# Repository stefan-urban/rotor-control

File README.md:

Rotor control with BeagleBone Black
===================================

Dieses Projekt entstand als Teil meiner Bachelorarbeit. Es zielt darauf ab ein Interface für zwei Antennenrotoren (unterschiedlicher Hersteller) zu bauen. Dieses soll eine Schnittstelle zu hamlib besitzen.

Vorraussetzungen
----------------

Hardware
- BeagleBone Black (=BBB)
- Cape wie unter dem Ordner `/hardware/eagle-project`
- Rotoren:
 - Create ERC5A (Elevation)
 - Yaesu G-2800DXC (Azimuth)

Software
- Debian 7.x mit
 - libpcre3-dev
 - libconfig-dev
 - libhamlib-utils (beinhaltet rotctl, rotctld)
- Auf dem Host-PC
 - Gpredict

Installation & Inbetriebnahme
-----------------------------

1. Software (unter `/software/`) aus diesem Repository in beliebigen Ordner auf dem BBB speichern.

2. (Optional) Konfigurationsfile unter `/etc/rotor_control.conf` anlegen. Eine Beispielkonfiguration ist im Ornder `docs` beigelegt.

3. (Optional) Rsyslogd konfigurieren.

 Standardmäßig werden alle Logging-Meldungen in `/var/log/syslog` mit allen anderen Meldungen vom System vermischt. Wie unser Programm ein eigene Logging-Datei erhält wird im beiliegenen Dokument [syslog.md](docs/syslog.md) erklärt.

5. Installieren
 ```
 debian@beaglebone:~/code/rotor-control/software$ sudo ./scripts/install.sh
 ```

 Jetzt werden alle erforderlichen Dateien in die entsprechenden Verzeichnise kopiert:
 - Programm und Start/Stop-Skripte nach `/opt/rotor-control/`
 - Daemon nach `/etc/init.d/`

6. Dienst starten
 ```
 debian@beaglebone:~/code/rotor-control/software$ sudo service rotor-control start
 ```

8. Verbindung mit gPredict aufbauen

 8.1. Gpredict starten
 
 8.2. Unter _Bearbeiten_ > _Einstellungen_ > _Interfaces_ > _Rotators_ einen neuen Rotor hinzufügen.
 
 8.3 Im Hauptfenster rechts oben auf den nach unten zeigenden Pfeil drücken und im erscheinenen Menü _Antennenkontrolle_ auswählen
 
 8.4 Es erscheint folgendes Fenster:

 8.5 Mit Drücken von _Kontakt_ wird die Verbindung zum BBB hergestellt und versucht die eingestellt Position anzufahren.

Verwendung ohne Rotoren
-----------------------

Zum Debugging ist es oft hilfreich das Programm __ohne__ die Rotorenanbindung zu betreiben. Dies ist möglich wenn in der Konfiguration die Simulation eingeschaltet wird. Dann wie oben beschrieben vorgehen.

Hintergrund: Als Rotorenansteuerung kommen jetzt nicht diverse GPIOs und ADCs zum Einsatz, welche es auf PCs gar nicht gibt, sondern ein Simulator.

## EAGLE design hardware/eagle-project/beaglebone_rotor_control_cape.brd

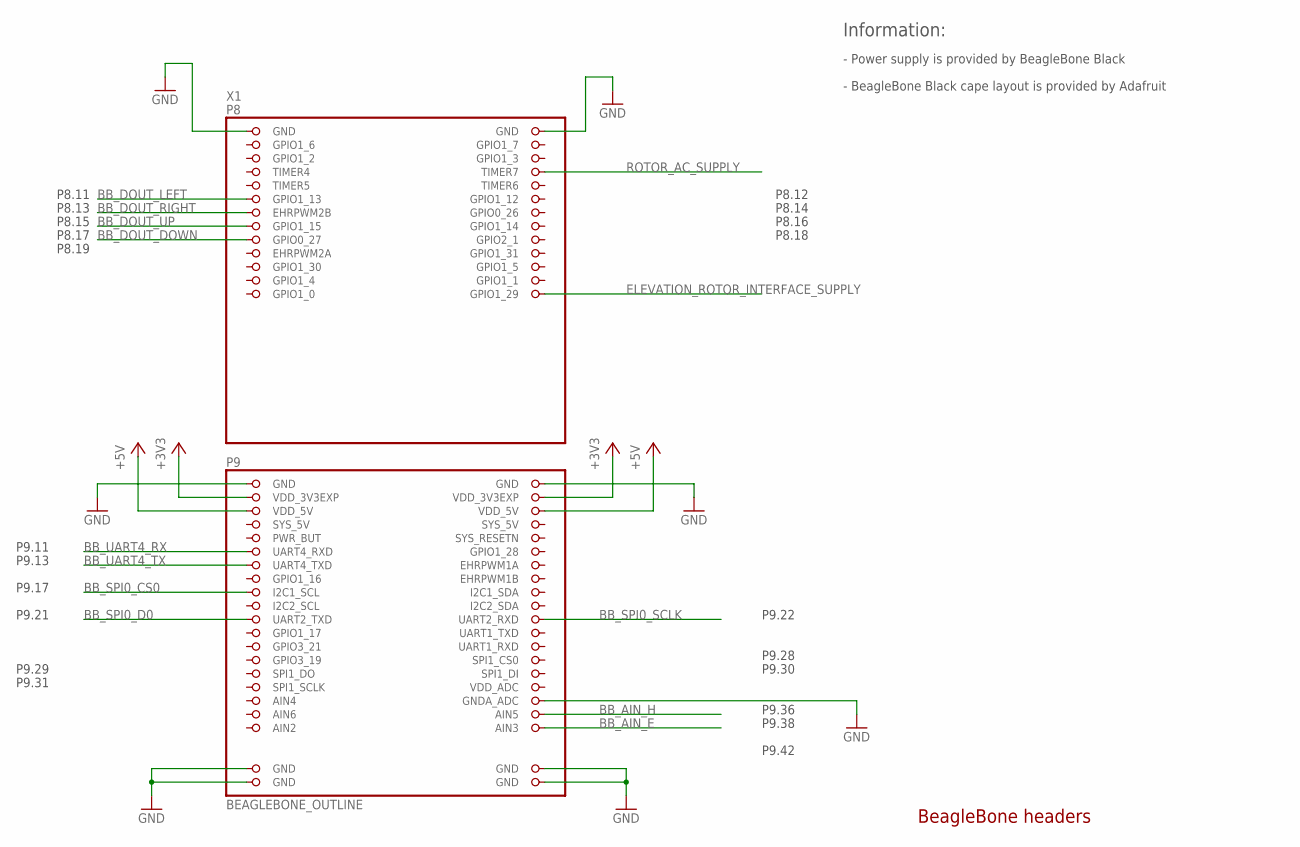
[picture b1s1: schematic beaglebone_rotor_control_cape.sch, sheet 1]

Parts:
X1: BEAGLEBONE_OUTLINE; BEAGLEBONE_SHIELD

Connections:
+3V3: X1.49 (VDD_3V3EXP), X1.50 (VDD_3V3EXP); also elsewhere on the board
+5V: X1.51 (VDD_5V), X1.52 (VDD_5V); also elsewhere on the board
BB_AIN_E: X1.84 (AIN3); also elsewhere on the board
BB_AIN_H: X1.82 (AIN5); also elsewhere on the board
BB_DOUT_DOWN: X1.17 (GPIO0_27); also elsewhere on the board
BB_DOUT_LEFT: X1.11 (GPIO1_13); also elsewhere on the board
BB_DOUT_RIGHT: X1.13 (EHRPWM2B); also elsewhere on the board
BB_DOUT_UP: X1.15 (GPIO1_15); also elsewhere on the board
BB_SPI0_CS0: X1.63 (I2C1_SCL); also elsewhere on the board
BB_SPI0_D0: X1.67 (UART2_TXD); also elsewhere on the board
BB_SPI0_SCLK: X1.68 (UART2_RXD); also elsewhere on the board
BB_UART4_RX: X1.57 (UART4_RXD); also elsewhere on the board
BB_UART4_TX: X1.59 (UART4_TXD); also elsewhere on the board
ELEVATION_ROTOR_INTERFACE_SUPPLY: X1.26 (GPIO1_29); also elsewhere on the board
GND: X1.1 (GND), X1.2 (GND), X1.47 (GND), X1.48 (GND), X1.80 (GNDA_ADC), X1.89 (GND), X1.90 (GND), X1.91 (GND), X1.92 (GND); also elsewhere on the board
ROTOR_AC_SUPPLY: X1.8 (TIMER7); also elsewhere on the board
SYS_5V: X1.53 (SYS_5V)

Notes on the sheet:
BeagleBone headers
- Power supply is provided by BeagleBone Black
Information:
- BeagleBone Black cape layout is provided by Adafruit
P9.17
P9.22
P9.21
P9.13
P9.11
P9.29
P9.30
P9.31
P9.28
P8.11
P8.13
P8.15
P8.17
P8.19
P8.12
P8.14
P8.16
P8.18
P9.36
P9.38
P9.42

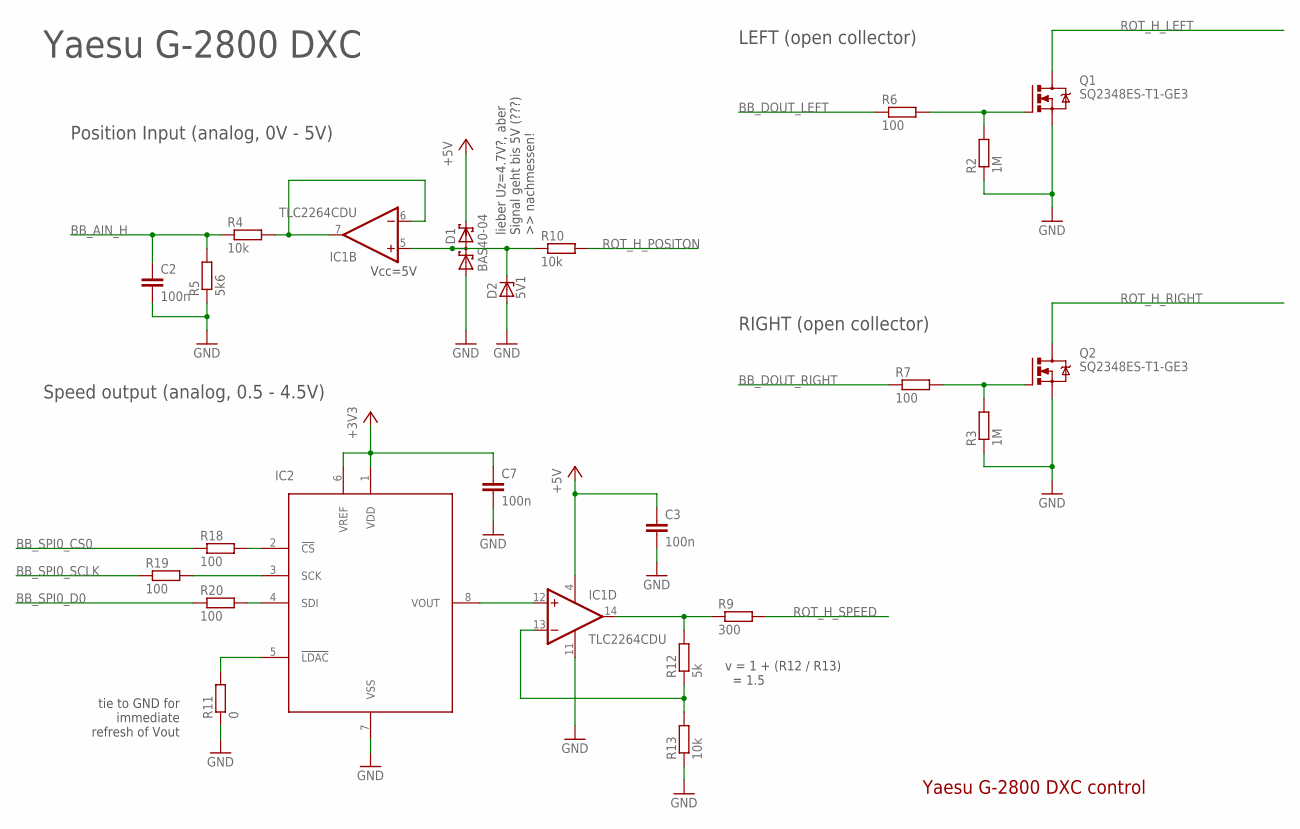
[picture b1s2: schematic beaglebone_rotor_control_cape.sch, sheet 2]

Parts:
C2, C3, C7: 100n; C0603
D1: BAS40-04; SOT23
D2: 5V1; SOT23
IC1: TLC2264CDU; SO14
IC2: MCP4901; SO-08
Q1, Q2: SQ2348ES-T1-GE3; SOT23
R2, R3: 1M; R0805
R4, R10, R13: 10k; R0805
R5: 5k6; R0805
R6, R7, R18, R19, R20: 100; R0805
R9: 300; R0805
R11: 0; R0805
R12: 5k; R0805

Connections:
+3V3: C7.1, IC2.1 (VDD), IC2.6 (VREF); also elsewhere on the board
+5V: C3.1, D1.2 (C2), IC1.4 (V+); also elsewhere on the board
BB_AIN_H: C2.1, R4.1, R5.2; also elsewhere on the board
BB_DOUT_LEFT: R6.1; also elsewhere on the board
BB_DOUT_RIGHT: R7.1; also elsewhere on the board
BB_SPI0_CS0: R18.1; also elsewhere on the board
BB_SPI0_D0: R20.1; also elsewhere on the board
BB_SPI0_SCLK: R19.1; also elsewhere on the board
GND: C2.2, C3.2, C7.2, D1.1 (A1), D2.1 (A), IC1.11 (V-), IC2.7 (VSS), Q1.2 (S), Q2.2 (S), R2.1, R3.1, R5.1, R11.1, R13.1; also elsewhere on the board
unnamed: IC1.6 (-IN), IC1.7 (OUT), R4.2
unnamed: IC1.12 (+IN), IC2.8 (VOUT)
unnamed: IC1.14 (OUT), R9.1, R12.2
unnamed: IC1.13 (-IN), R12.1, R13.2
unnamed: IC2.2 (!CS), R18.2
unnamed: IC2.5 (!LDAC), R11.2
unnamed: IC2.4 (SDI), R20.2
unnamed: IC2.3 (SCK), R19.2
unnamed: Q2.1 (G), R3.2, R7.2
unnamed: D1.3 (C1A2), D2.3 (C), IC1.5 (+IN), R10.1
unnamed: Q1.1 (G), R2.2, R6.2
ROT_H_LEFT: Q1.3 (D); also elsewhere on the board
ROT_H_POSITON: R10.2; also elsewhere on the board
ROT_H_RIGHT: Q2.3 (D); also elsewhere on the board
ROT_H_SPEED: R9.2; also elsewhere on the board

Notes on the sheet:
Yaesu G-2800 DXC control
LEFT (open collector)
RIGHT (open collector)
Position Input (analog, 0V - 5V)
Yaesu G-2800 DXC
Speed output (analog, 0.5 - 4.5V)
lieber Uz=4.7V?, aber Signal geht bis 5V (???) >> nachmessen!
Vcc=5V
tie to GND for immediate refresh of Vout
v = 1 + (R12 / R13) = 1.5

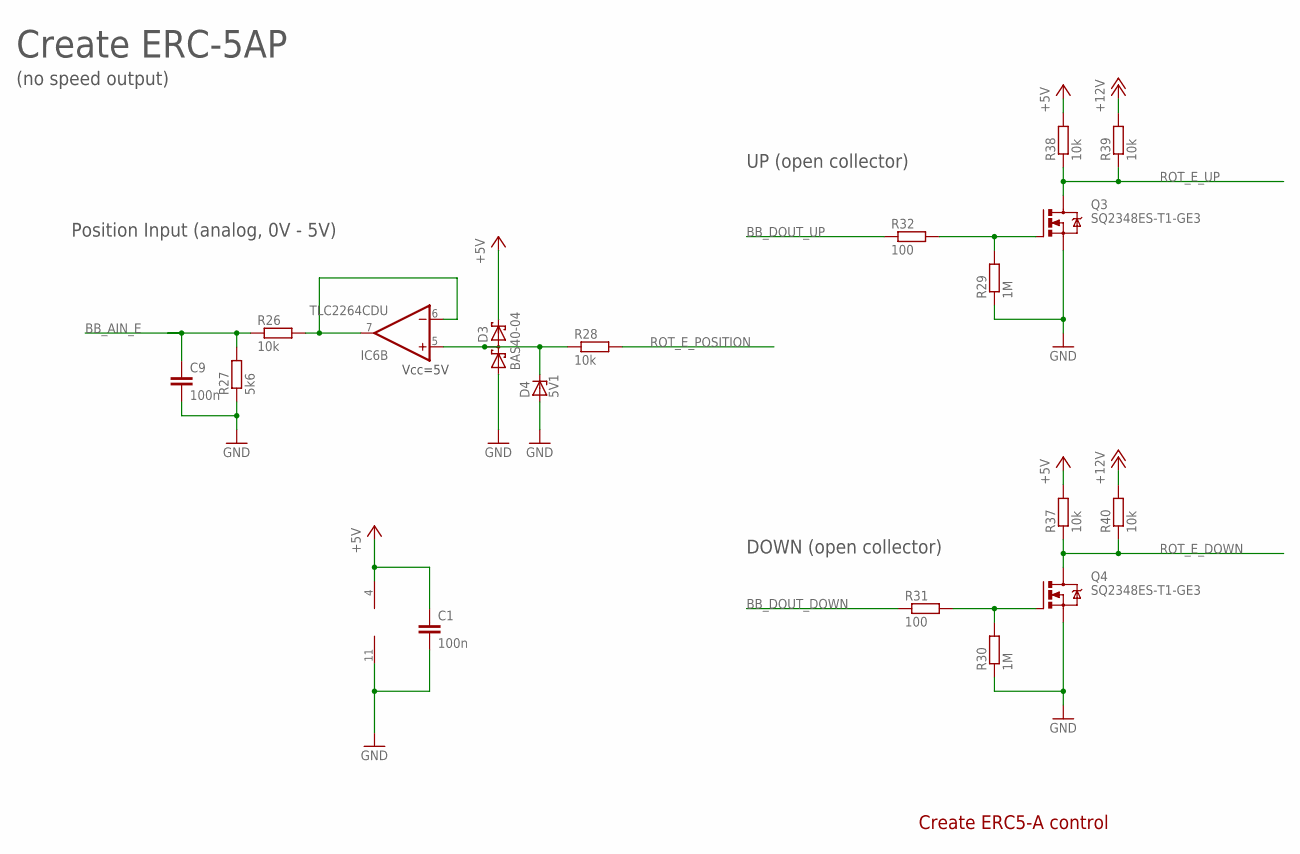
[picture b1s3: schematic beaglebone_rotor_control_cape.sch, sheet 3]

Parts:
C1, C9: 100n; C0603
D3: BAS40-04; SOT23
D4: 5V1; SOT23
IC6: TLC2264CDU; SO14
Q3, Q4: SQ2348ES-T1-GE3; SOT23
R26, R28, R37, R38, R39, R40: 10k; R0805
R27: 5k6; R0805
R29, R30: 1M; R0805
R31, R32: 100; R0805

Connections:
+5V: C1.1, D3.2 (C2), IC6.4 (V+), R37.2, R38.2; also elsewhere on the board
+12V: R39.2, R40.2; also elsewhere on the board
BB_AIN_E: C9.1, R26.1, R27.2; also elsewhere on the board
BB_DOUT_DOWN: R31.1; also elsewhere on the board
BB_DOUT_UP: R32.1; also elsewhere on the board
GND: C1.2, C9.2, D3.1 (A1), D4.1 (A), IC6.11 (V-), Q3.2 (S), Q4.2 (S), R27.1, R29.1, R30.1; also elsewhere on the board
unnamed: IC6.6 (-IN), IC6.7 (OUT), R26.2
unnamed: D3.3 (C1A2), D4.3 (C), IC6.5 (+IN), R28.1
unnamed: Q3.1 (G), R29.2, R32.2
unnamed: Q4.1 (G), R30.2, R31.2
ROT_E_DOWN: Q4.3 (D), R37.1, R40.1; also elsewhere on the board
ROT_E_POSITION: R28.2; also elsewhere on the board
ROT_E_UP: Q3.3 (D), R38.1, R39.1; also elsewhere on the board

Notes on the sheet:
Create ERC5-A control
Position Input (analog, 0V - 5V)
Vcc=5V
Create ERC-5AP
UP (open collector)
DOWN (open collector)
(no speed output)

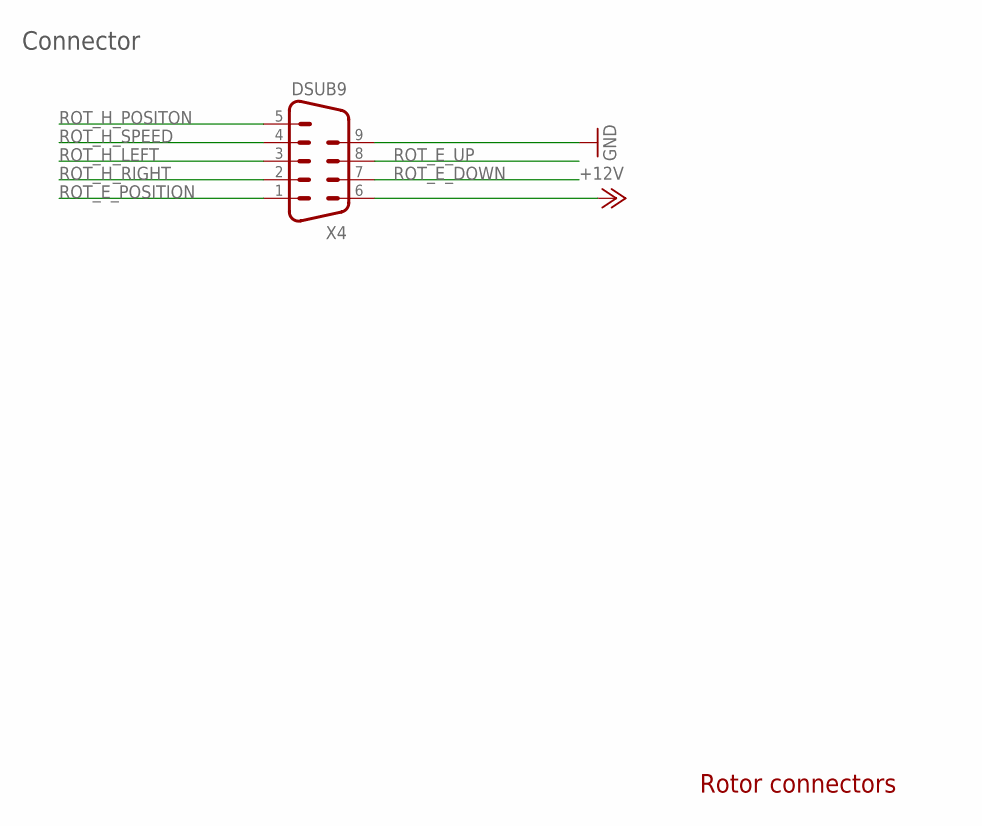
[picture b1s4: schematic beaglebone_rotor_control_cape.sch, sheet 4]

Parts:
X4: DSUB9

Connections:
+12V: X4.6; also elsewhere on the board
GND: X4.9; also elsewhere on the board
ROT_E_DOWN: X4.7; also elsewhere on the board
ROT_E_POSITION: X4.1; also elsewhere on the board
ROT_E_UP: X4.8; also elsewhere on the board
ROT_H_LEFT: X4.3; also elsewhere on the board
ROT_H_POSITON: X4.5; also elsewhere on the board
ROT_H_RIGHT: X4.2; also elsewhere on the board
ROT_H_SPEED: X4.4; also elsewhere on the board

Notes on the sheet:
Rotor connectors
Connector

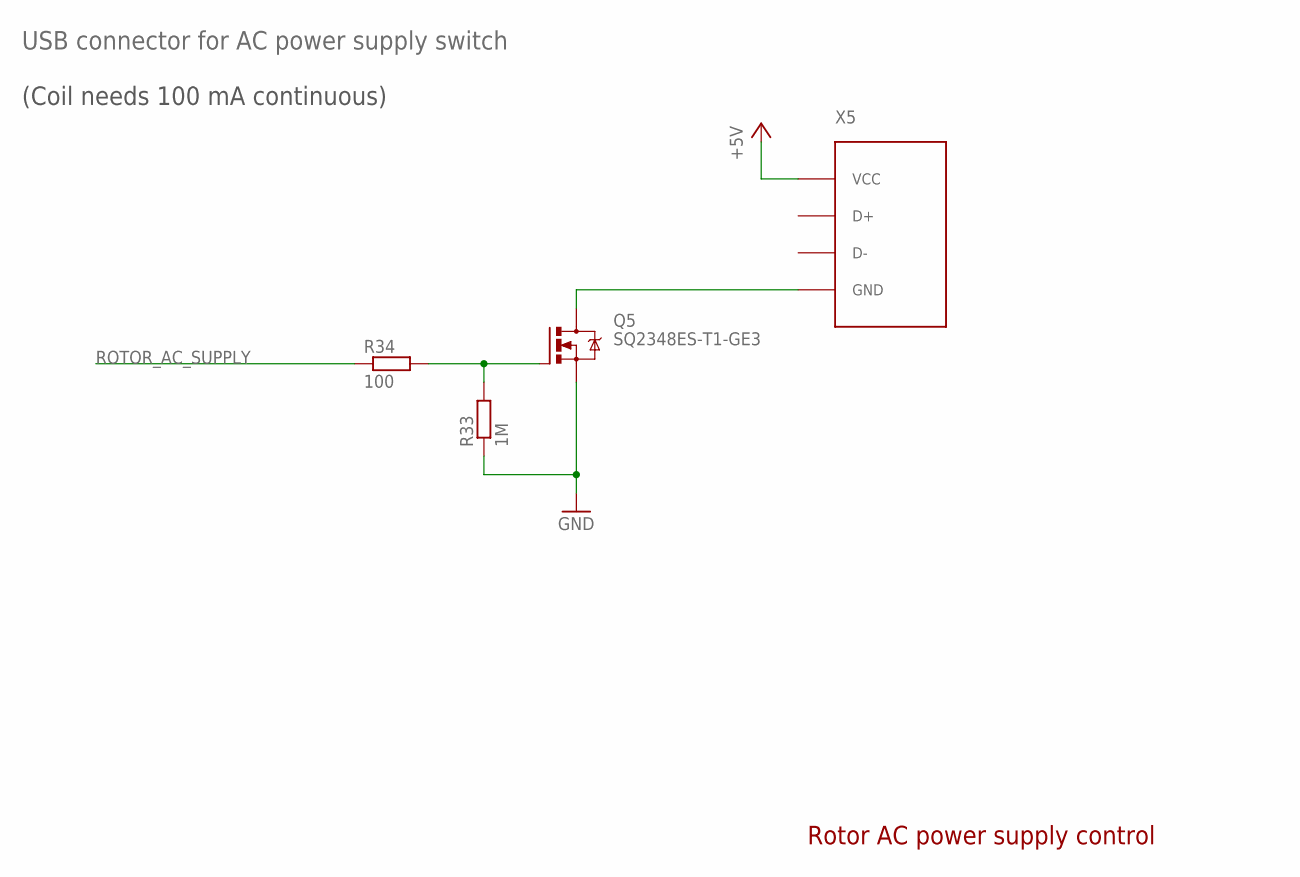
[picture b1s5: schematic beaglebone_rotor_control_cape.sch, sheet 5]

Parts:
Q5: SQ2348ES-T1-GE3; SOT23
R33: 1M; R0805
R34: 100; R0805
X5: USBDEV; USB

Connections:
+5V: X5.1-VCC (VCC); also elsewhere on the board
GND: Q5.2 (S), R33.1; also elsewhere on the board
unnamed: Q5.3 (D), X5.GND
unnamed: Q5.1 (G), R33.2, R34.2
ROTOR_AC_SUPPLY: R34.1; also elsewhere on the board

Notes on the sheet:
Rotor AC power supply control
USB connector for AC power supply switch
(Coil needs 100 mA continuous)

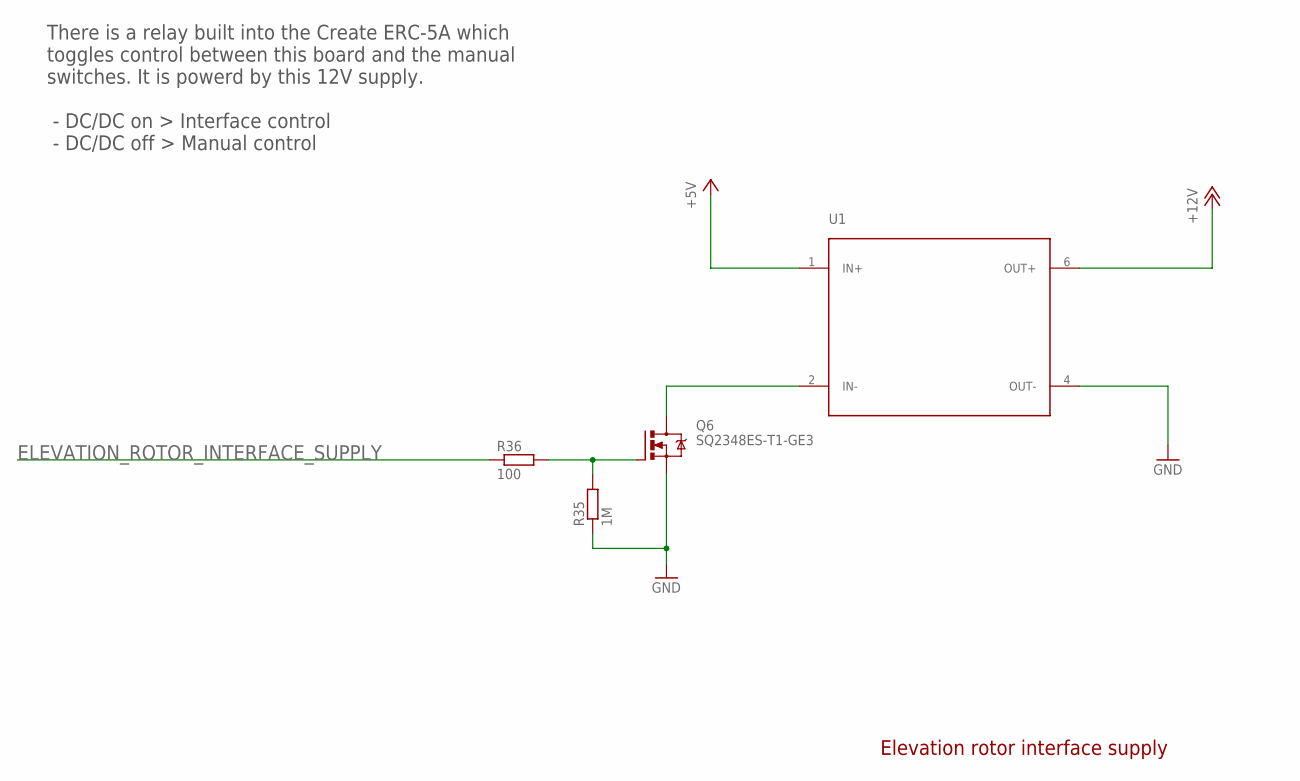
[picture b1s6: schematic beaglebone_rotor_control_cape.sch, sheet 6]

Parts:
Q6: SQ2348ES-T1-GE3; SOT23
R35: 1M; R0805
R36: 100; R0805
U1: TMH0512S; SIP

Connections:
+5V: U1.1 (IN+); also elsewhere on the board
+12V: U1.6 (OUT+); also elsewhere on the board
ELEVATION_ROTOR_INTERFACE_SUPPLY: R36.1; also elsewhere on the board
GND: Q6.2 (S), R35.1, U1.4 (OUT-); also elsewhere on the board
unnamed: Q6.1 (G), R35.2, R36.2
unnamed: Q6.3 (D), U1.2 (IN-)

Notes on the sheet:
Elevation rotor interface supply
There is a relay built into the Create ERC-5A which toggles control between this board and the manual switches. It is powerd by this 12V supply. - DC/DC on > Interface control - DC/DC off > Manual control

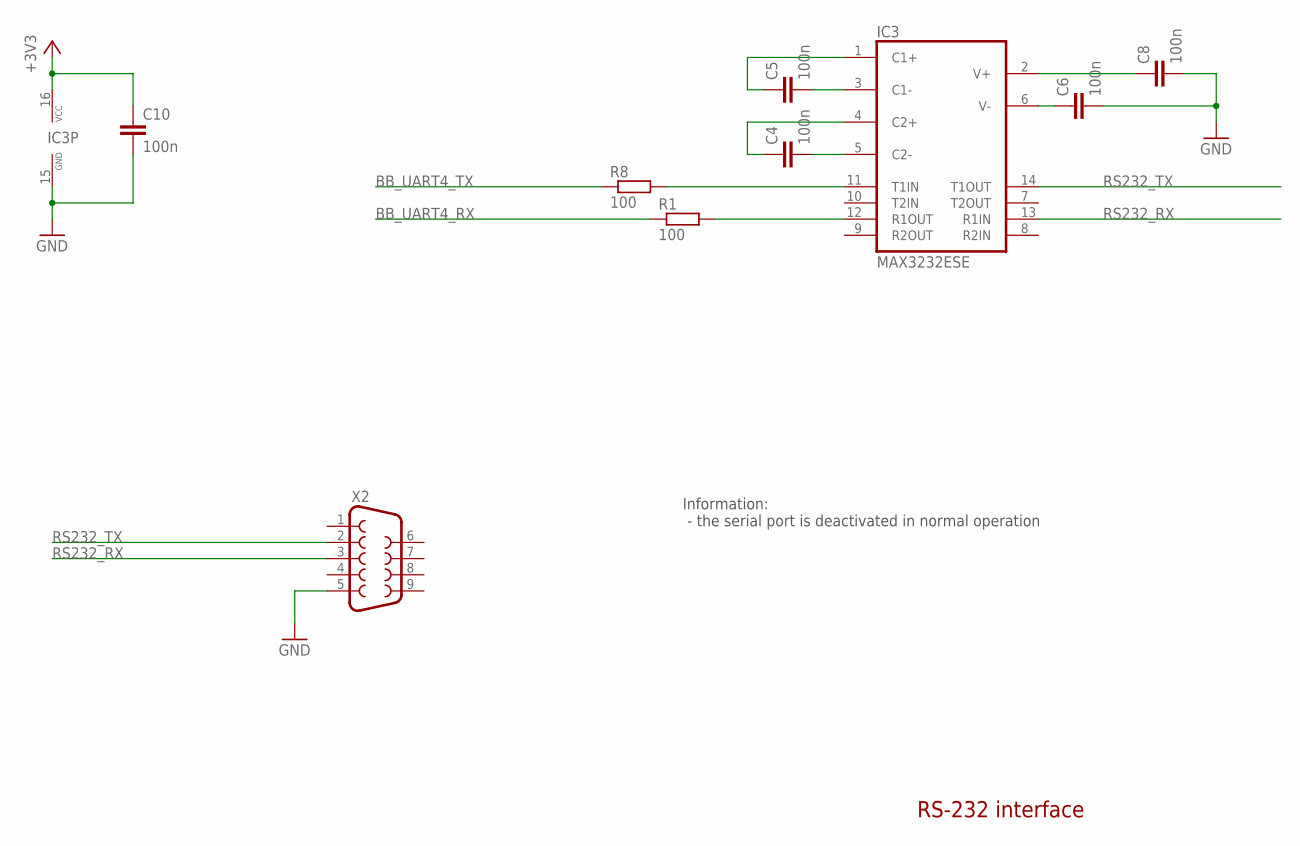
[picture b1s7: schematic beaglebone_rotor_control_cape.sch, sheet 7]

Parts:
C4, C5, C6, C8, C10: 100n; C0603
IC3: MAX3232ESE; SO16
R1, R8: 100; R0805
X2: F09VP

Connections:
+3V3: C10.1, IC3.16 (VCC); also elsewhere on the board
BB_UART4_RX: R1.1; also elsewhere on the board
BB_UART4_TX: R8.1; also elsewhere on the board
GND: C6.2, C8.2, C10.2, IC3.15 (GND), X2.5; also elsewhere on the board
unnamed: C4.1, IC3.4 (C2+)
unnamed: C4.2, IC3.5 (C2-)
unnamed: C5.2, IC3.3 (C1-)
unnamed: C5.1, IC3.1 (C1+)
unnamed: C6.1, IC3.6 (V-)
unnamed: C8.1, IC3.2 (V+)
unnamed: IC3.11 (T1IN), R8.2
unnamed: IC3.12 (R1OUT), R1.2
RS232_RX: IC3.13 (R1IN), X2.3
RS232_TX: IC3.14 (T1OUT), X2.2

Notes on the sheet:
RS-232 interface
Information: - the serial port is deactivated in normal operation

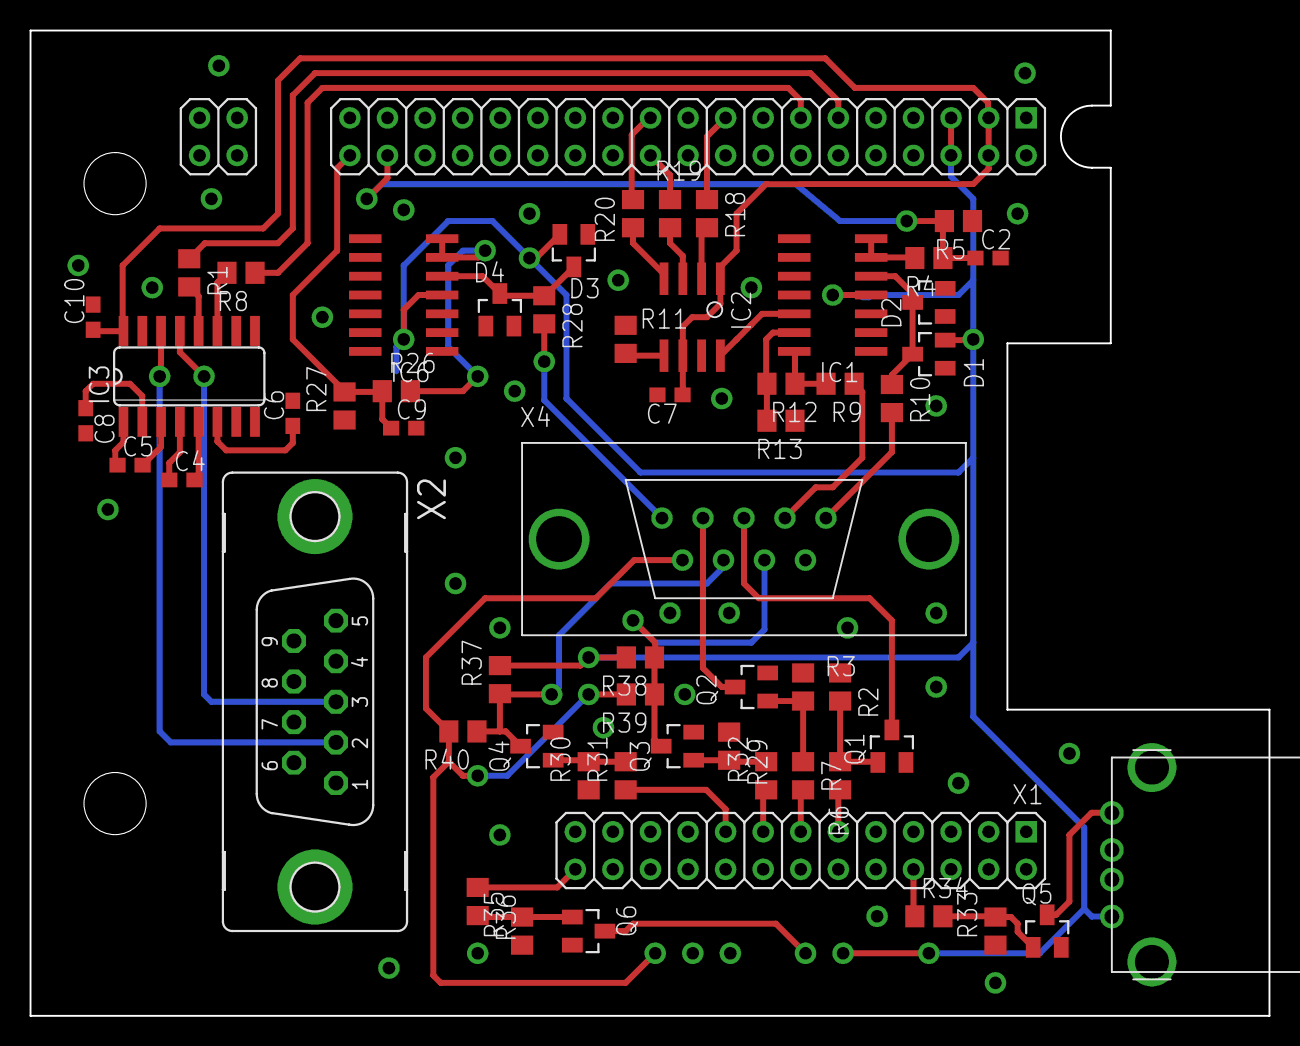
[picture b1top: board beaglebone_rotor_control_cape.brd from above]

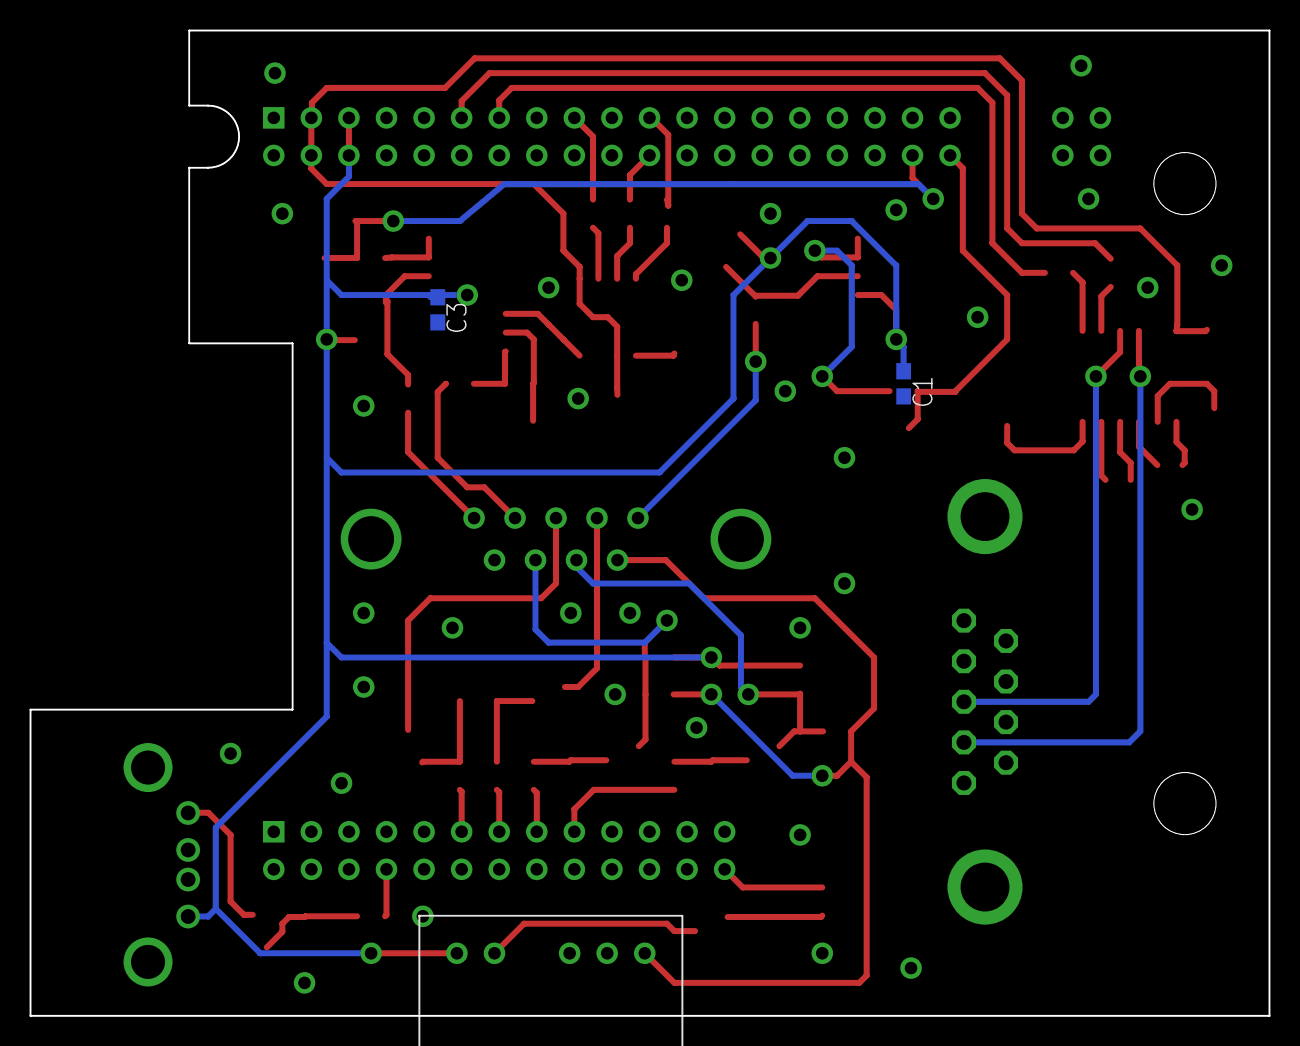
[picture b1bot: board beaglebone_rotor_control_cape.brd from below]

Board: 2 copper layers, 83.8 x 66.6 mm, 60 parts (3 on the bottom side), 53 nets.

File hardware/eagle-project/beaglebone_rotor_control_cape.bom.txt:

Stückliste exportiert aus /home/stefan/Repositories/rotor-control/hardware/eagle-project/beaglebone_rotor_control_cape.sch am 31.08.14 10:45

Part Value              Device             Package           Description                                      
C1   100n               C-EUC0603          C0603             CAPACITOR, European symbol                       
C2   100n               C-EUC0603          C0603             CAPACITOR, European symbol                       
C3   100n               C-EUC0603          C0603             CAPACITOR, European symbol                       
C4   100n               C-EUC0603          C0603             CAPACITOR, European symbol                       
C5   100n               C-EUC0603          C0603             CAPACITOR, European symbol                       
C6   100n               C-EUC0603          C0603             CAPACITOR, European symbol                       
C7   100n               C-EUC0603          C0603             CAPACITOR, European symbol                       
C8   100n               C-EUC0603          C0603             CAPACITOR, European symbol                       
C9   100n               C-EUC0603          C0603             CAPACITOR, European symbol                       
C10  100n               C-EUC0603          C0603             CAPACITOR, European symbol                       
D1   BAS40-04           BAS40-04           SOT23             Silicon Schottky Diodes                          
D2   5V1                ZENER-DIODESOT23   SOT23             Z-Diode                                          
D3   BAS40-04           BAS40-04           SOT23             Silicon Schottky Diodes                          
D4   5V1                ZENER-DIODESOT23   SOT23             Z-Diode                                          
IC1  TLC2264CDU         TLC2264CDU         SO14              Quad Operational Amplifier                       
IC2  MCP4901            MCP4901            SO-08             8-Bit Voltage Output                             
IC3  MAX3232ESE         MAX3232ESE         SO16              True RS-232 Transceivers 3.0V to 5.5V, Low-Power 
IC6  TLC2264CDU         TLC2264CDU         SO14              Quad Operational Amplifier                       
Q1   SQ2348ES-T1-GE3    SQ2348ES-T1-GE3    SOT23             Automotive N-Channel MOSFET                      
Q2   SQ2348ES-T1-GE3    SQ2348ES-T1-GE3    SOT23             Automotive N-Channel MOSFET                      
Q3   SQ2348ES-T1-GE3    SQ2348ES-T1-GE3    SOT23             Automotive N-Channel MOSFET                      
Q4   SQ2348ES-T1-GE3    SQ2348ES-T1-GE3    SOT23             Automotive N-Channel MOSFET                      
Q5   SQ2348ES-T1-GE3    SQ2348ES-T1-GE3    SOT23             Automotive N-Channel MOSFET                      
Q6   SQ2348ES-T1-GE3    SQ2348ES-T1-GE3    SOT23             Automotive N-Channel MOSFET                      
R1   100                R-EU_R0805         R0805             RESISTOR, European symbol                        
R2   1M                 R-EU_R0805         R0805             RESISTOR, European symbol                        
R3   1M                 R-EU_R0805         R0805             RESISTOR, European symbol                        
R4   10k                R-EU_R0805         R0805             RESISTOR, European symbol                        
R5   5k6                R-EU_R0805         R0805             RESISTOR, European symbol                        
R6   100                R-EU_R0805         R0805             RESISTOR, European symbol                        
R7   100                R-EU_R0805         R0805             RESISTOR, European symbol                        
R8   100                R-EU_R0805         R0805             RESISTOR, European symbol                        
R9   100                R-EU_R0805         R0805             RESISTOR, European symbol                        
R10  10k                R-EU_R0805         R0805             RESISTOR, European symbol                        
R11  0                  R-EU_R0805         R0805             RESISTOR, European symbol                        
R12  5k                 R-EU_R0805         R0805             RESISTOR, European symbol                        
R13  10k                R-EU_R0805         R0805             RESISTOR, European symbol                        
R18  100                R-EU_R0805         R0805             RESISTOR, European symbol                        
R19  100                R-EU_R0805         R0805             RESISTOR, European symbol                        
R20  100                R-EU_R0805         R0805             RESISTOR, European symbol                        
R26  10k                R-EU_R0805         R0805             RESISTOR, European symbol                        
R27  5k6                R-EU_R0805         R0805             RESISTOR, European symbol                        
R28  10k                R-EU_R0805         R0805             RESISTOR, European symbol                        
R29  1M                 R-EU_R0805         R0805             RESISTOR, European symbol                        
R30  1M                 R-EU_R0805         R0805             RESISTOR, European symbol                        
R31  100                R-EU_R0805         R0805             RESISTOR, European symbol                        
R32  100                R-EU_R0805         R0805             RESISTOR, European symbol                        
R33  1M                 R-EU_R0805         R0805             RESISTOR, European symbol                        
R34  100                R-EU_R0805         R0805             RESISTOR, European symbol                        
R35  1M                 R-EU_R0805         R0805             RESISTOR, European symbol                        
R36  100                R-EU_R0805         R0805             RESISTOR, European symbol                        
R37  10k                R-EU_R0805         R0805             RESISTOR, European symbol                        
R38  10k                R-EU_R0805         R0805             RESISTOR, European symbol                        
R39  10k                R-EU_R0805         R0805             RESISTOR, European symbol                        
R40  10k                R-EU_R0805         R0805             RESISTOR, European symbol                        
U1   TMH0512S           TMH0512S           SIP               DC/DC Converter - TMH Series, 2 Watt             
X1   BEAGLEBONE_OUTLINE BEAGLEBONE_OUTLINE BEAGLEBONE_SHIELD BeagleBone Black Reference Layout                
X2                      F09VP              F09VP             SUB-D                                            
X4   DSUB9              DSUB9              DSUB9             3-1634222-2                                      
X5   USBDEV             USBDEV             USB               USB Buchse - Typ A, abgewinkelt

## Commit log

2014-05-15 Installation script now check library dependencies
2014-05-15 Fixed uninteded cast
2014-05-15 Changed ADC channels to the ones on the PCB (was configured for breadboard setup)
2014-05-15 Tried to configure elevation position sensor, switch to real rotors
2014-05-15 Install configuration file
2014-05-15 Fixed debug messages for rotor moving direction (UP, DOWN, ...)
2014-05-15 Changed position return syntax to be hamlib compatible
2014-05-15 Fixed error in command line parsing
2014-05-15 Implemented ADC AIN5 & AIN6 for testing, reaction on 'Get position' command visible
2014-05-15 Created GPIOs according to Eagle schematic
2014-05-15 SPI communication implemented
2014-05-15 A few tests with GPIOs
2014-05-15 Changed GPIO numbers to the correct one, now works
2014-05-26 main programm created, opens pseudo terminal and reads from it, not working good (wip, lunch break)
2014-06-13 main.c
2014-06-13 * converted tabs to spaces, bad use of multiple editors
2014-06-13 * outsourced pseudoterminal handling to seperate files
2014-06-13 * forgot to add main.c in last commit
2014-06-13 * added gs232 interface * problems with serial port, maybe problems with configuration?
2014-06-20 Moved software into own folder
2014-06-20 Added eagle files (libraries, design rule check, schematics and layout)
2014-06-23 Eagle project update * RS232 rcv/drv layout done * AMP Press-Fit connector library created
2014-06-23 Updated available components list
2014-06-24 README update
2014-06-24 First draft for DAC interface
2014-06-24 New comments/thoughts in EAGLE schematics
2014-06-24 Added specifications for TI TLV5616 in c-file chip may not be suitable for our application, maybe switch to Microchip MCP4901?
2014-06-24 I did not mean to merge dac into master but vice versa
2014-06-24 Welcome back old branch files
2014-06-24 Changed DAC from TI TLV5616 to Microchip MCP4901
2014-06-24 Added software draft for MCP4901 and some Eagle schematic updates
2014-06-24 Created Makefile
2014-06-24 Various fixes in dac code
2014-06-24 Added speed dummy commands to GS-232 interface
2014-06-25 Added clean commando to Makefile
2014-06-25 Working on DAC interface
2014-06-25 Removed TI TLV5616 files because of Microchip MCP4901 usage
2014-06-25 Documentation folder added
2014-06-25 Deleted editor backup file and modified gitignore to prevent commit
2014-06-25 Merges changes from dac to master
2014-06-26 Fixed break condition on main program
2014-06-26 Deleted unnecessary functions
2014-06-27 Hardware: Create ERC5-AP interface
2014-06-27 Added link to device tree overlay sources
2014-06-27 Fixed code block indicator in doc file
2014-06-27 Integrated post-DAC amplifier
2014-06-27 First draft of GPIO interface, testing needed
2014-07-02 created gpio test branch
2014-07-21 Current GPIO usage in userspace is a fail
2014-07-21 test
2014-07-21 test gitignore
2014-07-21 Test commit which should be pushed to all remotes
2014-07-23 Deleted GPIO in userspace and updated GS232 interface
2014-07-24 * layout: added spi1 and determined pin for usb slave turn on
2014-07-25 Fixed some strange merge errors
2014-07-25 Makefile now just compiles all *.c files
2014-07-28 Created library for D-Sub connector from TE.com
2014-07-28 Placed D-Sub connectors on layout
2014-07-28 Added USB connector
2014-07-29 new GPIO test
2014-07-29 Updated schematic
2014-07-31 Updated eagle schematic
2014-08-06 Added DCDC to eagle schematic and made first draft of layout
2014-08-07 Improved Eagle layout, more free space on board for future components
2014-08-11 Tweaked eagle layout for easier manufacturing
2014-08-17 Optical tweaks for eagle schematic
2014-08-17 Added serial interface chip to layout
2014-08-18 Eagle layout update finalized for manufacturing
2014-08-24 Added debugging component based on syslog
2014-08-24 Debugging is now implemented in everything
2014-08-24 Updated debugging functions
2014-08-24 Implemented configuration file and command line options, fixed error in makefile
2014-08-24 Refactored ADC function
2014-08-24 Minor fixes
2014-08-24 Code cleanup
2014-08-24 Program no longer quits when no configuration file is found
2014-08-25 Changed abstraction layers completely, added debug rotor for offline testing
2014-08-25 Minor fixes and cleanups
2014-08-25 Debug rotor is now able to set position via 'Wxxx yyy' command.
2014-08-26 Rotors now support 'set position' command. Position sensor evaluation enhanced
2014-08-26 Installation instructions in README.md
2014-08-26 Added software requirements
2014-08-26 Added configuration sample file
2014-08-28 Set position function of elevation rotor was not included in rotors struct
2014-08-31 Created BOM
2014-08-31 Created schematic overview over power supply
2014-08-31 Software now tries to publish pseudoterminal path to /var/run
2014-09-08 Fixed typo
2014-09-08 Changed short circuit protection resitor
2014-09-08 Elevation rotor principle
2014-09-13 Added debugging information to executable
2014-09-13 Interpolation table support in master
2014-09-13 Changed gray schematic color to black for better documentation readability
2014-09-13 Fixed interpolation errors
2014-09-14 Added missing configuration parameters
2014-09-14 Optical adjustments
2014-09-14 Added lots of commentation
2014-09-14 New folder structure
2014-09-14 Changed replys to ok and renamed executable to rotor-control
2014-09-14 Added signal action for SIGKILL and SIGTERM
2014-09-14 Updated instructions
2014-09-14 Added scripts folder
2014-09-14 Tweaked installation script
2014-09-14 Inserted measured values
2015-03-04 fixed image location in readme file
2015-03-10 Tweaked service startup file
2015-03-10 Fixed communication errors with multiple applications accessing rotor_control pts file
2015-03-24 Implementation of pseudoterminal configuration variable
2015-03-24 added travis ci config file
2015-03-24 fixed yml file format
2015-03-24 created travis specific compile script
2015-03-24 deleted old compile script
2015-03-24 updated travis config file to use dedicated compile script
2015-03-24 yml syntax error
2015-03-24 Updated travis dependencies and included build status icon in README
2015-03-24 apt-get update fix
2015-03-24 travis fix
2015-03-24 travis debug
2015-03-24 Resolved travis libconfig version complications
2015-03-24 fixed travis config
2015-03-24 make code libconfig version dependent
2015-03-24 and again travis fix
2015-03-24 Fixed compilation error and removed compile script again
2015-03-24 Added support for multiple pseudoterminal creation, config file based
2015-03-24 Create LICENSE
2015-04-02 (Un-)Installation enhancements
